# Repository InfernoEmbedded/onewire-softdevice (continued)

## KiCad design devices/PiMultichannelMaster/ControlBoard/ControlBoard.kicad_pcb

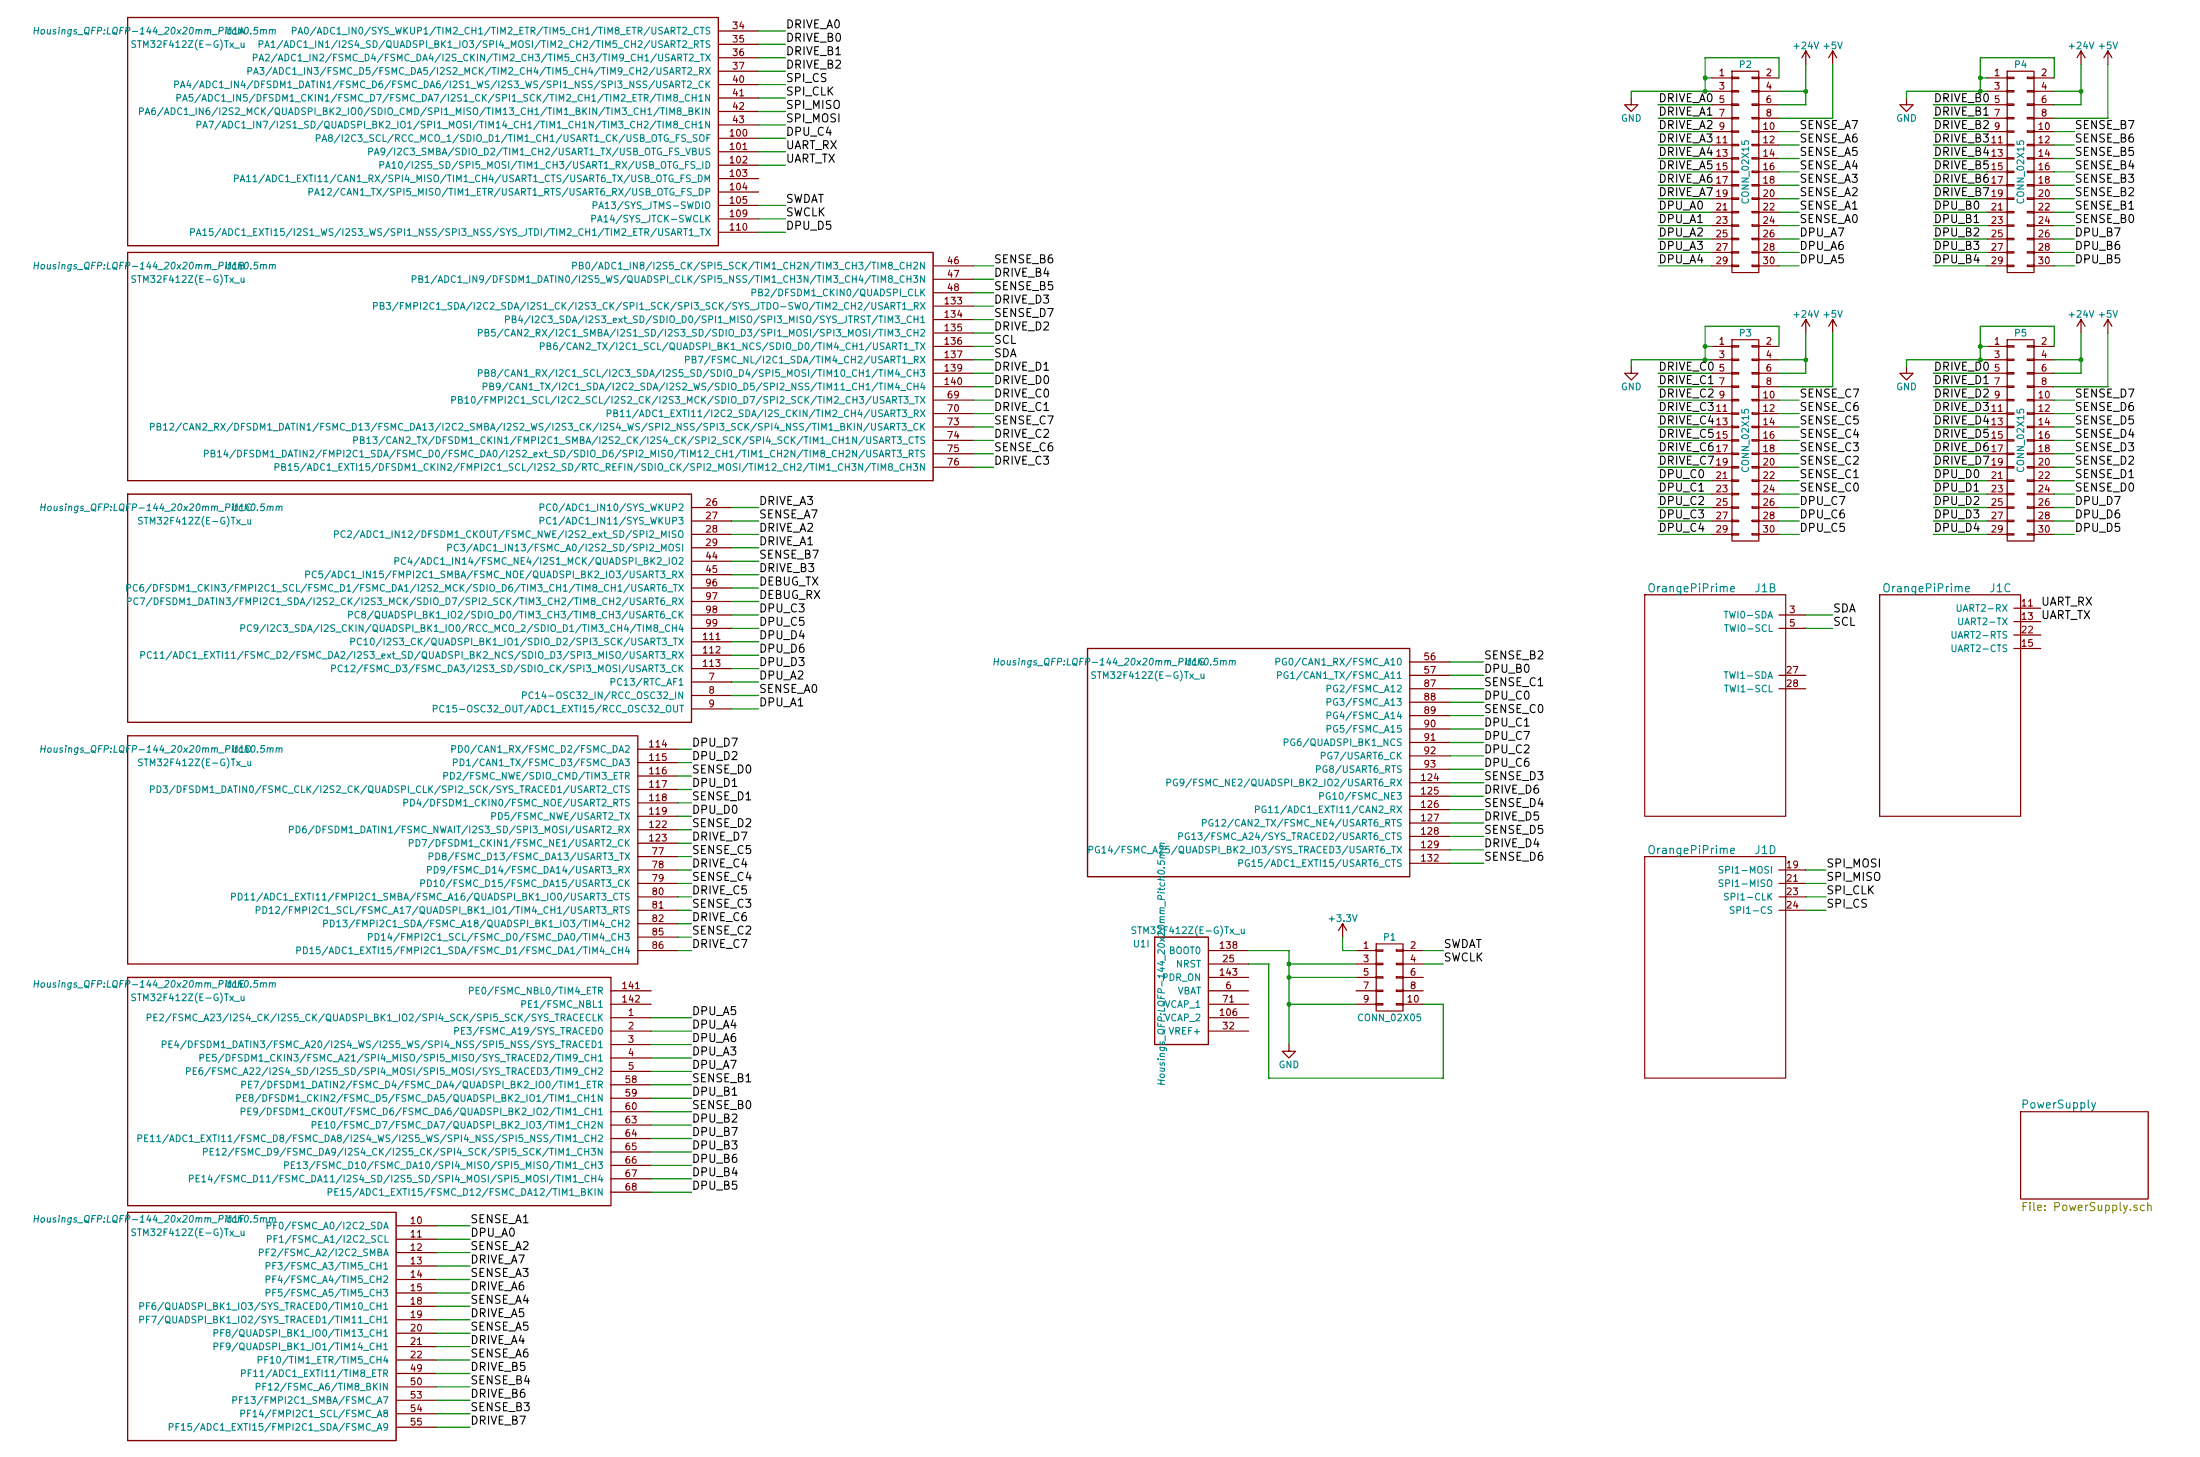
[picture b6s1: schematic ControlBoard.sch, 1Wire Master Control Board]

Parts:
J1: OrangePiPrime
P1: CONN_02X05; Pin_Header_Straight_2x05_Pitch2.54mm_SMD
P2, P3, P4, P5: CONN_02X15; Pin_Header_Straight_2x15_Pitch2.54mm_SMD
U1: STM32F412Z(E-G)Tx_u; LQFP-144_20x20mm_Pitch0.5mm

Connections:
+3V3: P1.1; also elsewhere on the board
+5V: P2.8, P3.8, P4.8, P5.8; also elsewhere on the board
+24V: P2.4, P2.6, P3.4, P3.6, P4.4, P4.6, P5.4, P5.6; also elsewhere on the board
/DPU_A0: P2.21, U1.11 (PF1/FSMC_A1/I2C2_SCL)
/DPU_A1: P2.23, U1.9 (PC15-OSC32_OUT/ADC1_EXTI15/RCC_OSC32_OUT)
/DPU_A2: P2.25, U1.7 (PC13/RTC_AF1)
/DPU_A3: P2.27, U1.4 (PE5/DFSDM1_CKIN3/FSMC_A21/SPI4_MISO/SPI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)
/DPU_A4: P2.29, U1.2 (PE3/FSMC_A19/SYS_TRACED0)
/DPU_A5: P2.30, U1.1 (PE2/FSMC_A23/I2S4_CK/I2S5_CK/QUADSPI_BK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)
/DPU_A6: P2.28, U1.3 (PE4/DFSDM1_DATIN3/FSMC_A20/I2S4_WS/I2S5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)
/DPU_A7: P2.26, U1.5 (PE6/FSMC_A22/I2S4_SD/I2S5_SD/SPI4_MOSI/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)
/DPU_B0: P4.21, U1.57 (PG1/CAN1_TX/FSMC_A11)
/DPU_B1: P4.23, U1.59 (PE8/DFSDM1_CKIN2/FSMC_D5/FSMC_DA5/QUADS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)
/DPU_B2: P4.25, U1.63 (PE10/FSMC_D7/FSMC_DA7/QUADSPI_BK2_IO3/T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)
/DPU_B3: P4.27, U1.65 (PE12/FSMC_D9/FSMC_DA9/I2S4_CK/I2S5_CK/S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)
/DPU_B4: P4.29, U1.67 (PE14/FSMC_D11/FSMC_DA11/I2S4_SD/I2S5_SD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)
/DPU_B5: P4.30, U1.68 (PE15/ADC1_EXTI15/FSMC_D12/FSMC_DA12/TIM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)
/DPU_B6: P4.28, U1.66 (PE13/FSMC_D10/FSMC_DA10/SPI4_MISO/SPI5_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)
/DPU_B7: P4.26, U1.64 (PE11/ADC1_EXTI11/FSMC_D8/FSMC_DA8/I2S4_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)
/DPU_C0: P3.21, U1.88 (PG3/FSMC_A13)
/DPU_C1: P3.23, U1.90 (PG5/FSMC_A15)
/DPU_C2: P3.25, U1.92 (PG7/USART6_CK)
/DPU_C3: P3.27, U1.98 (PC8/QUADSPI_BK1_IO2/SDIO_D0/TIM3_CH3/TI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)
/DPU_C4: P3.29, U1.100 (PA8/I2C3_SCL/RCC_MCO_1/SDIO_D1/TIM1_CH1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)
/DPU_C5: P3.30, U1.99 (PC9/I2C3_SDA/I2S_CKIN/QUADSPI_BK1_IO0/R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)
/DPU_C6: P3.28, U1.93 (PG8/USART6_RTS)
/DPU_C7: P3.26, U1.91 (PG6/QUADSPI_BK1_NCS)
/DPU_D0: P5.21, U1.119 (PD5/FSMC_NWE/USART2_TX)
/DPU_D1: P5.23, U1.117 (PD3/DFSDM1_DATIN0/FSMC_CLK/I2S2_CK/QUAD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)
/DPU_D2: P5.25, U1.115 (PD1/CAN1_TX/FSMC_D3/FSMC_DA3)
/DPU_D3: P5.27, U1.113 (PC12/FSMC_D3/FSMC_DA3/I2S3_SD/SDIO_CK/S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)
/DPU_D4: P5.29, U1.111 (PC10/I2S3_CK/QUADSPI_BK1_IO1/SDIO_D2/SP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)
/DPU_D5: P5.30, U1.110 (PA15/ADC1_EXTI15/I2S1_WS/I2S3_WS/SPI1_N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)
/DPU_D6: P5.28, U1.112 (PC11/ADC1_EXTI11/FSMC_D2/FSMC_DA2/I2S3_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)
/DPU_D7: P5.26, U1.114 (PD0/CAN1_RX/FSMC_D2/FSMC_DA2)
/DRIVE_A0: P2.5, U1.34 (PA0/ADC1_IN0/SYS_WKUP1/TIM2_CH1/TIM2_ET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)
/DRIVE_A1: P2.7, U1.29 (PC3/ADC1_IN13/FSMC_A0/I2S2_SD/SPI2_MOSI)
/DRIVE_A2: P2.9, U1.28 (PC2/ADC1_IN12/DFSDM1_CKOUT/FSMC_NWE/I2S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)
/DRIVE_A3: P2.11, U1.26 (PC0/ADC1_IN10/SYS_WKUP2)
/DRIVE_A4: P2.13, U1.21 (PF9/QUADSPI_BK1_IO1/TIM14_CH1)
/DRIVE_A5: P2.15, U1.19 (PF7/QUADSPI_BK1_IO2/SYS_TRACED1/TIM11_C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)
/DRIVE_A6: P2.17, U1.15 (PF5/FSMC_A5/TIM5_CH3)
/DRIVE_A7: P2.19, U1.13 (PF3/FSMC_A3/TIM5_CH1)
/DRIVE_B0: P4.5, U1.35 (PA1/ADC1_IN1/I2S4_SD/QUADSPI_BK1_IO3/SP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)
/DRIVE_B1: P4.7, U1.36 (PA2/ADC1_IN2/FSMC_D4/FSMC_DA4/I2S_CKIN/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)
/DRIVE_B2: P4.9, U1.37 (PA3/ADC1_IN3/FSMC_D5/FSMC_DA5/I2S2_MCK/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)
/DRIVE_B3: P4.11, U1.45 (PC5/ADC1_IN15/FMPI2C1_SMBA/FSMC_NOE/QUA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)
/DRIVE_B4: P4.13, U1.47 (PB1/ADC1_IN9/DFSDM1_DATIN0/I2S5_WS/QUAD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)
/DRIVE_B5: P4.15, U1.49 (PF11/ADC1_EXTI11/TIM8_ETR)
/DRIVE_B6: P4.17, U1.53 (PF13/FMPI2C1_SMBA/FSMC_A7)
/DRIVE_B7: P4.19, U1.55 (PF15/ADC1_EXTI15/FMPI2C1_SDA/FSMC_A9)
/DRIVE_C0: P3.5, U1.69 (PB10/FMPI2C1_SCL/I2C2_SCL/I2S2_CK/I2S3_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)
/DRIVE_C1: P3.7, U1.70 (PB11/ADC1_EXTI11/I2C2_SDA/I2S_CKIN/TIM2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)
/DRIVE_C2: P3.9, U1.74 (PB13/CAN2_TX/DFSDM1_CKIN1/FMPI2C1_SMBA/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)
/DRIVE_C3: P3.11, U1.76 (PB15/ADC1_EXTI15/DFSDM1_CKIN2/FMPI2C1_S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)
/DRIVE_C4: P3.13, U1.78 (PD9/FSMC_D14/FSMC_DA14/USART3_RX)
/DRIVE_C5: P3.15, U1.80 (PD11/ADC1_EXTI11/FMPI2C1_SMBA/FSMC_A16/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)
/DRIVE_C6: P3.17, U1.82 (PD13/FMPI2C1_SDA/FSMC_A18/QUADSPI_BK1_I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)
/DRIVE_C7: P3.19, U1.86 (PD15/ADC1_EXTI15/FMPI2C1_SDA/FSMC_D1/FS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)
/DRIVE_D0: P5.5, U1.140 (PB9/CAN1_TX/I2C1_SDA/I2C2_SDA/I2S2_WS/S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)
/DRIVE_D1: P5.7, U1.139 (PB8/CAN1_RX/I2C1_SCL/I2C3_SDA/I2S5_SD/S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)
/DRIVE_D2: P5.9, U1.135 (PB5/CAN2_RX/I2C1_SMBA/I2S1_SD/I2S3_SD/S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)
/DRIVE_D3: P5.11, U1.133 (PB3/FMPI2C1_SDA/I2C2_SDA/I2S1_CK/I2S3_C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)
/DRIVE_D4: P5.13, U1.129 (PG14/FSMC_A25/QUADSPI_BK2_IO3/SYS_TRACE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)
/DRIVE_D5: P5.15, U1.127 (PG12/CAN2_TX/FSMC_NE4/USART6_RTS)
/DRIVE_D6: P5.17, U1.125 (PG10/FSMC_NE3)
/DRIVE_D7: P5.19, U1.123 (PD7/DFSDM1_CKIN1/FSMC_NE1/USART2_CK)
/SCL: J1.5 (TWI0-SCL), U1.136 (PB6/CAN2_TX/I2C1_SCL/QUADSPI_BK1_NCS/SD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)
/SDA: J1.3 (TWI0-SDA), U1.137 (PB7/FSMC_NL/I2C1_SDA/TIM4_CH2/USART1_RX)
/SENSE_A0: P2.24, U1.8 (PC14-OSC32_IN/RCC_OSC32_IN)
/SENSE_A1: P2.22, U1.10 (PF0/FSMC_A0/I2C2_SDA)
/SENSE_A2: P2.20, U1.12 (PF2/FSMC_A2/I2C2_SMBA)
/SENSE_A3: P2.18, U1.14 (PF4/FSMC_A4/TIM5_CH2)
/SENSE_A4: P2.16, U1.18 (PF6/QUADSPI_BK1_IO3/SYS_TRACED0/TIM10_C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)
/SENSE_A5: P2.14, U1.20 (PF8/QUADSPI_BK1_IO0/TIM13_CH1)
/SENSE_A6: P2.12, U1.22 (PF10/TIM1_ETR/TIM5_CH4)
/SENSE_A7: P2.10, U1.27 (PC1/ADC1_IN11/SYS_WKUP3)
/SENSE_B0: P4.24, U1.60 (PE9/DFSDM1_CKOUT/FSMC_D6/FSMC_DA6/QUADS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)
/SENSE_B1: P4.22, U1.58 (PE7/DFSDM1_DATIN2/FSMC_D4/FSMC_DA4/QUAD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)
/SENSE_B2: P4.20, U1.56 (PG0/CAN1_RX/FSMC_A10)
/SENSE_B3: P4.18, U1.54 (PF14/FMPI2C1_SCL/FSMC_A8)
/SENSE_B4: P4.16, U1.50 (PF12/FSMC_A6/TIM8_BKIN)
/SENSE_B5: P4.14, U1.48 (PB2/DFSDM1_CKIN0/QUADSPI_CLK)
/SENSE_B6: P4.12, U1.46 (PB0/ADC1_IN8/I2S5_CK/SPI5_SCK/TIM1_CH2N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)
/SENSE_B7: P4.10, U1.44 (PC4/ADC1_IN14/FSMC_NE4/I2S1_MCK/QUADSPI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)
/SENSE_C0: P3.24, U1.89 (PG4/FSMC_A14)
/SENSE_C1: P3.22, U1.87 (PG2/FSMC_A12)
/SENSE_C2: P3.20, U1.85 (PD14/FMPI2C1_SCL/FSMC_D0/FSMC_DA0/TIM4_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)
/SENSE_C3: P3.18, U1.81 (PD12/FMPI2C1_SCL/FSMC_A17/QUADSPI_BK1_I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)
/SENSE_C4: P3.16, U1.79 (PD10/FSMC_D15/FSMC_DA15/USART3_CK)
/SENSE_C5: P3.14, U1.77 (PD8/FSMC_D13/FSMC_DA13/USART3_TX)
/SENSE_C6: P3.12, U1.75 (PB14/DFSDM1_DATIN2/FMPI2C1_SDA/FSMC_D0/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)
/SENSE_C7: P3.10, U1.73 (PB12/CAN2_RX/DFSDM1_DATIN1/FSMC_D13/FSM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)
/SENSE_D0: P5.24, U1.116 (PD2/FSMC_NWE/SDIO_CMD/TIM3_ETR)
/SENSE_D1: P5.22, U1.118 (PD4/DFSDM1_CKIN0/FSMC_NOE/USART2_RTS)
/SENSE_D2: P5.20, U1.122 (PD6/DFSDM1_DATIN1/FSMC_NWAIT/I2S3_SD/SP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)
/SENSE_D3: P5.18, U1.124 (PG9/FSMC_NE2/QUADSPI_BK2_IO2/USART6_RX)
/SENSE_D4: P5.16, U1.126 (PG11/ADC1_EXTI11/CAN2_RX)
/SENSE_D5: P5.14, U1.128 (PG13/FSMC_A24/SYS_TRACED2/USART6_CTS)
/SENSE_D6: P5.12, U1.132 (PG15/ADC1_EXTI15/USART6_CTS)
/SENSE_D7: P5.10, U1.134 (PB4/I2C3_SDA/I2S3_ext_SD/SDIO_D0/SPI1_M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)
/SPI_CLK: J1.23 (SPI1-CLK), U1.41 (PA5/ADC1_IN5/DFSDM1_CKIN1/FSMC_D7/FSMC_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)
/SPI_CS: J1.24 (SPI1-CS), U1.40 (PA4/ADC1_IN4/DFSDM1_DATIN1/FSMC_D6/FSMC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)
/SPI_MISO: J1.21 (SPI1-MISO), U1.42 (PA6/ADC1_IN6/I2S2_MCK/QUADSPI_BK2_IO0/S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)
/SPI_MOSI: J1.19 (SPI1-MOSI), U1.43 (PA7/ADC1_IN7/I2S1_SD/QUADSPI_BK2_IO1/SP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)
/SWCLK: P1.4, U1.109 (PA14/SYS_JTCK-SWCLK)
/SWDAT: P1.2, U1.105 (PA13/SYS_JTMS-SWDIO)
/UART_RX: J1.11 (UART2-RX), U1.101 (PA9/I2C3_SMBA/SDIO_D2/TIM1_CH2/USART1_T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)
/UART_TX: J1.13 (UART2-TX), U1.102 (PA10/I2S5_SD/SPI5_MOSI/TIM1_CH3/USART1_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)
GND: P1.3, P1.5, P1.9, P2.1, P2.2, P2.3, P3.1, P3.2, P3.3, P4.1, P4.2, P4.3, P5.1, P5.2, P5.3, U1.138 (BOOT0); also elsewhere on the board
unnamed: P1.10, U1.25 (NRST)

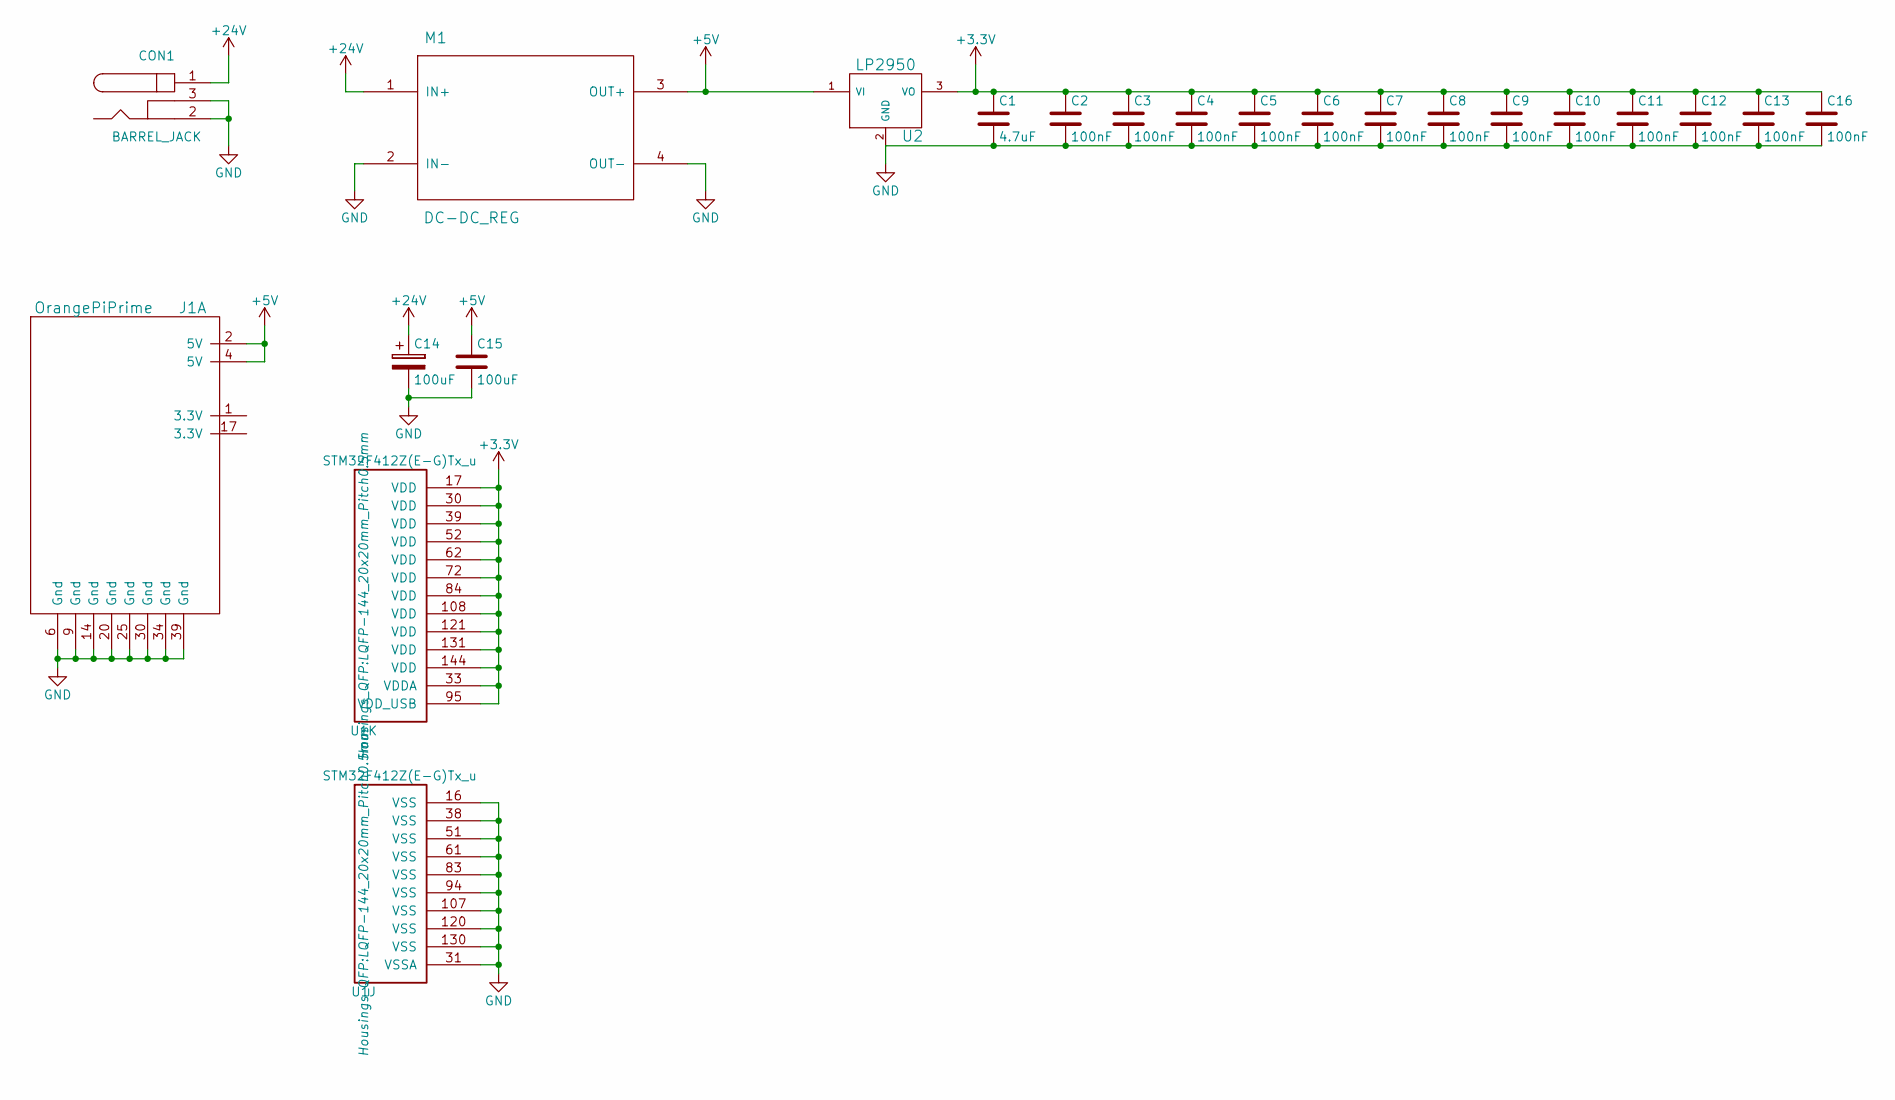
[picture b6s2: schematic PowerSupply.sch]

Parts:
C1: 4.7uF; C_0603
C2, C3, C4, C5, C6, C7, C8, C9, C10, C11, C12, C13, C16: 100nF; C_0603
C14: 100uF; CP_Elec_8x10
C15: 100uF; C_1206
CON1: BARREL_JACK
J1: OrangePiPrime
M1: DC-DC_REG; D-SUN_DC_DC
U1: STM32F412Z(E-G)Tx_u; LQFP-144_20x20mm_Pitch0.5mm
U2: LP2950; TO-252-2

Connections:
+3V3: C1.1, C2.1, C3.1, C4.1, C5.1, C6.1, C7.1, C8.1, C9.1, C10.1, C11.1, C12.1, C13.1, C16.1, U1.17 (VDD), U1.30 (VDD), U1.33 (VDDA), U1.39 (VDD), U1.52 (VDD), U1.62 (VDD), U1.72 (VDD), U1.84 (VDD), U1.95 (VDD_USB), U1.108 (VDD), U1.121 (VDD), U1.131 (VDD), U1.144 (VDD), U2.3 (VO); also elsewhere on the board
+5V: C15.1, J1.2 (5V), J1.4 (5V), M1.3 (OUT+), U2.1 (VI); also elsewhere on the board
+24V: C14.1, CON1.1, M1.1 (IN+); also elsewhere on the board
GND: C1.2, C2.2, C3.2, C4.2, C5.2, C6.2, C7.2, C8.2, C9.2, C10.2, C11.2, C12.2, C13.2, C14.2, C15.2, C16.2, CON1.2, CON1.3, J1.6 (Gnd), J1.9 (Gnd), J1.14 (Gnd), J1.20 (Gnd), J1.25 (Gnd), J1.30 (Gnd), J1.34 (Gnd), J1.39 (Gnd), M1.2 (IN-), M1.4 (OUT-), U1.16 (VSS), U1.31 (VSSA), U1.38 (VSS), U1.51 (VSS), U1.61 (VSS), U1.83 (VSS), U1.94 (VSS), U1.107 (VSS), U1.120 (VSS), U1.130 (VSS), U2.2 (GND); also elsewhere on the board

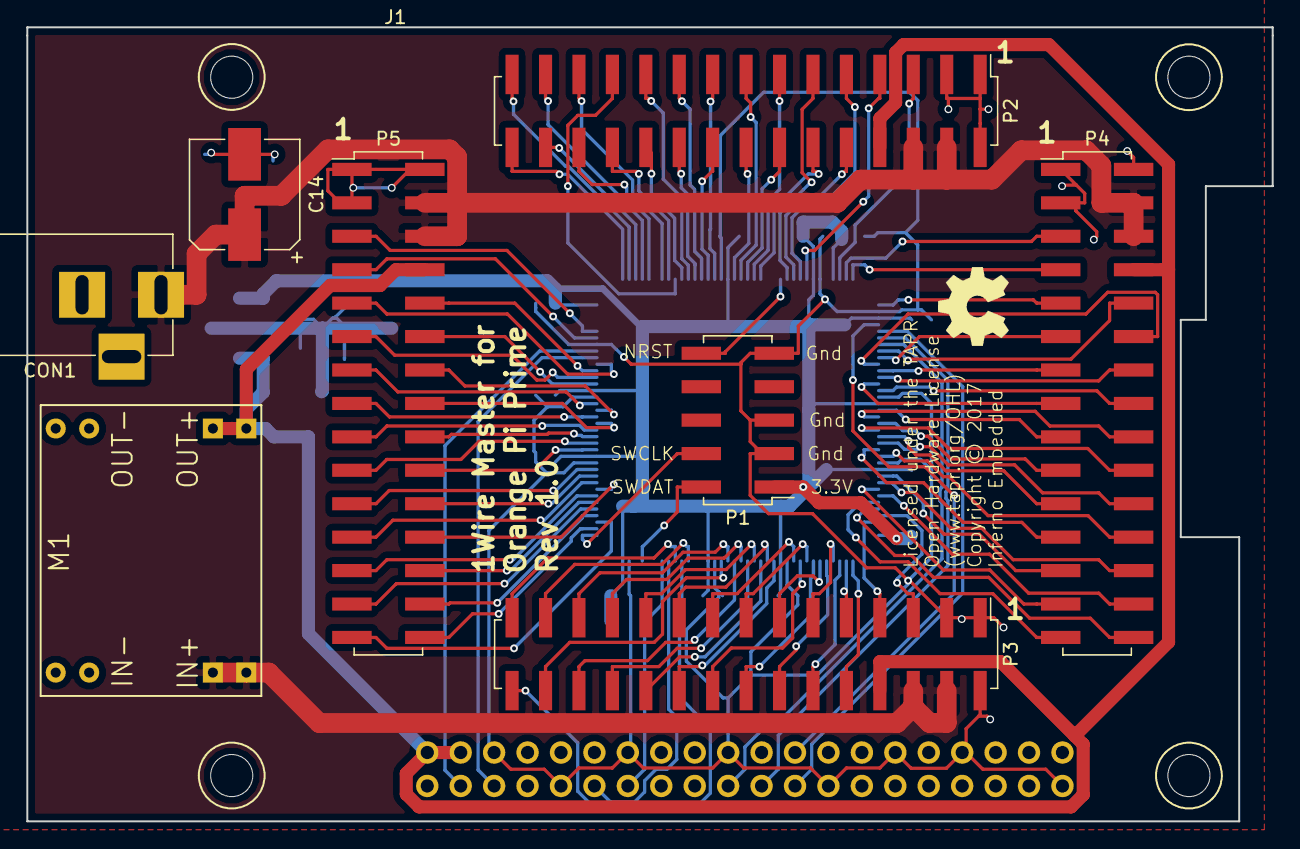
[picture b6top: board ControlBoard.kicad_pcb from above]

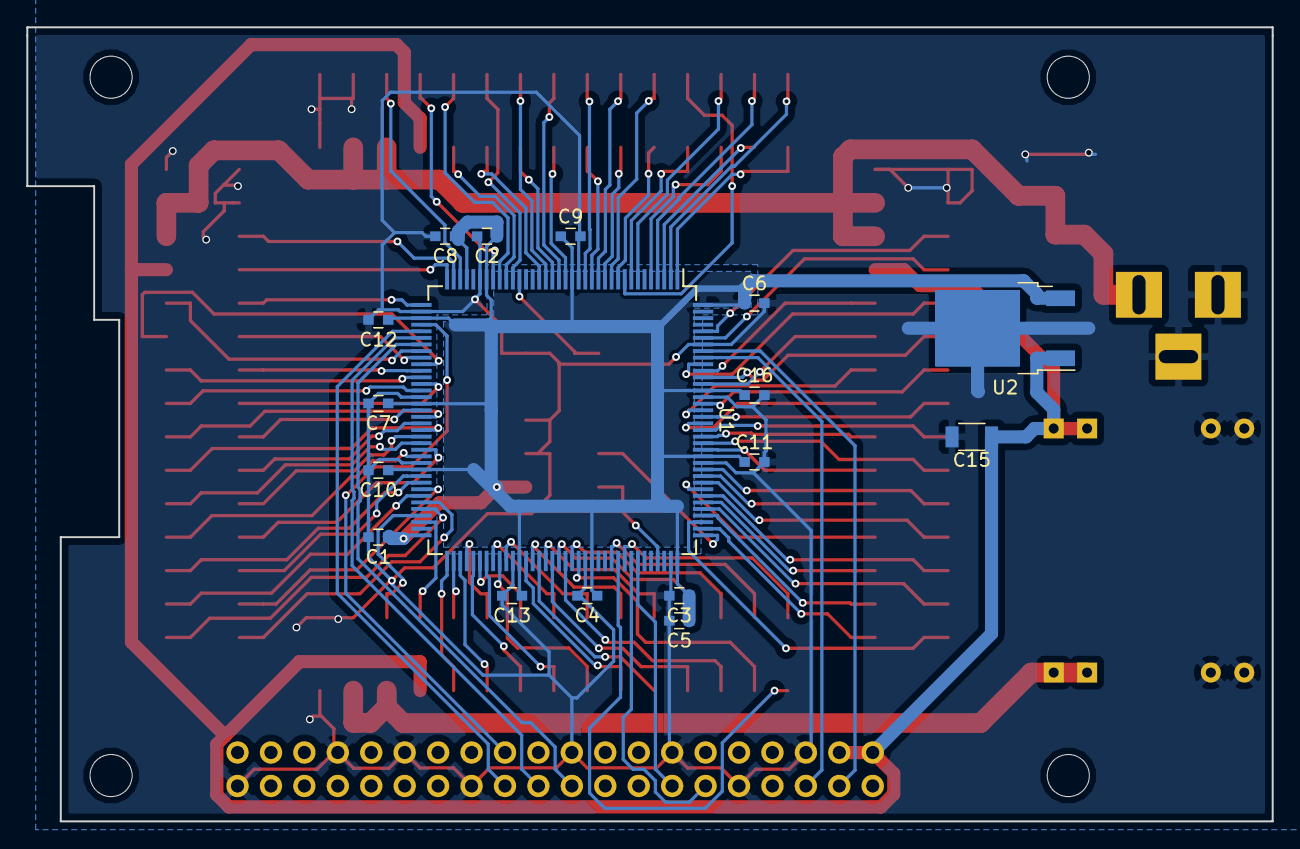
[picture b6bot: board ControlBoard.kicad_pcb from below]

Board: 2 copper layers, 94.6 x 60.3 mm, 30 parts (17 on the bottom side), 111 nets.

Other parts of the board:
REF1, REF2, REF3, REF4: MountingHole_3.2mm_M3

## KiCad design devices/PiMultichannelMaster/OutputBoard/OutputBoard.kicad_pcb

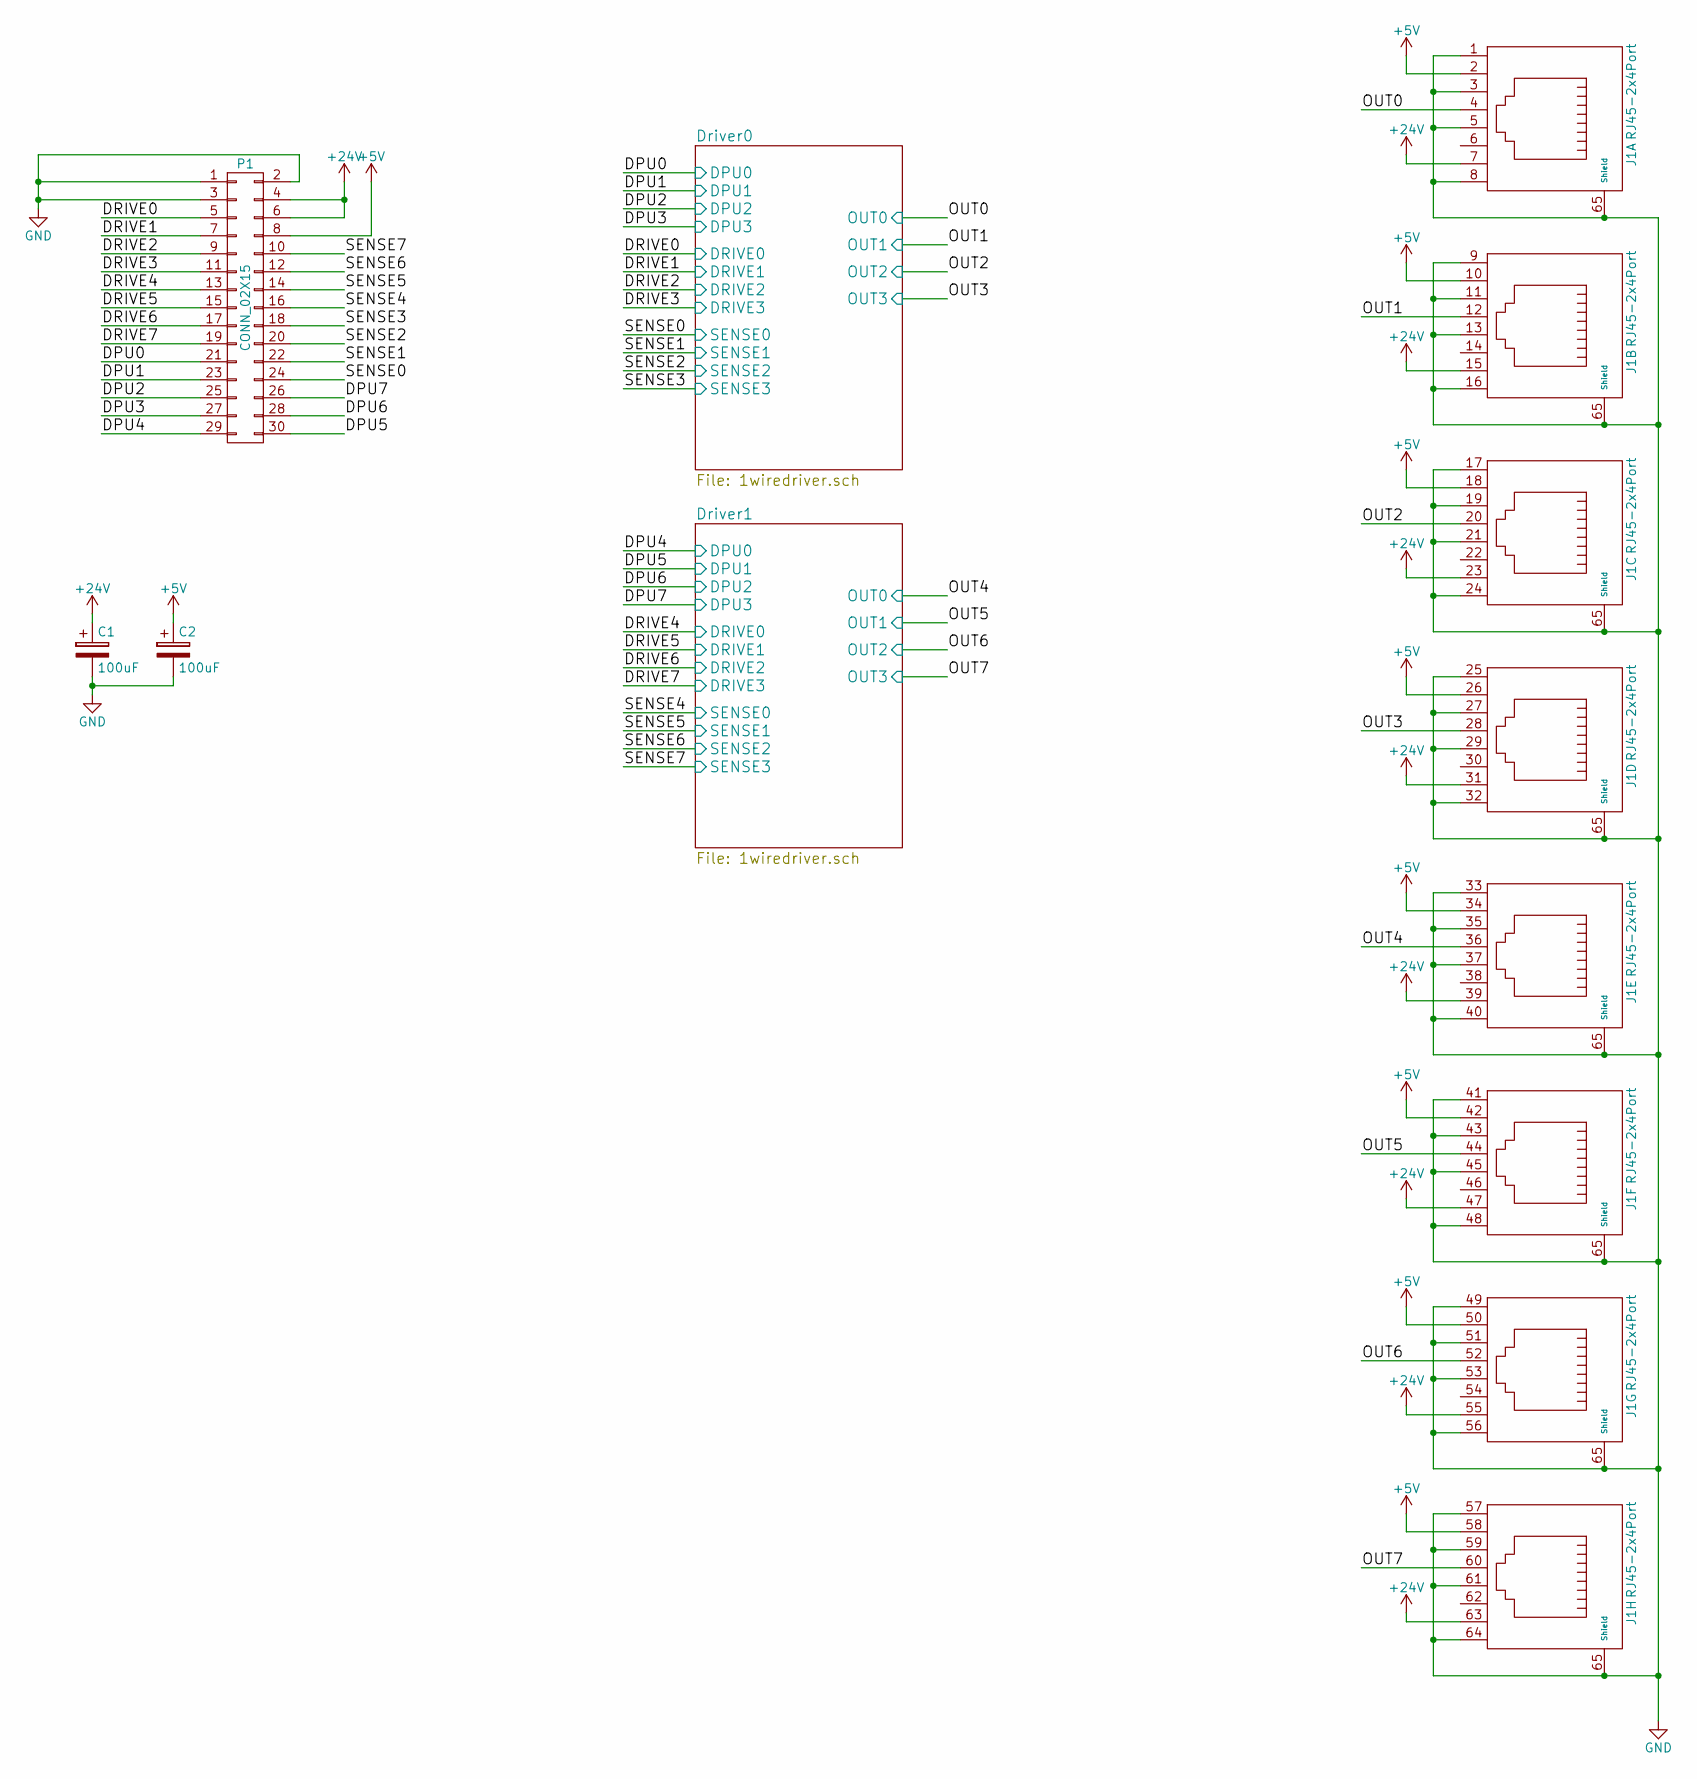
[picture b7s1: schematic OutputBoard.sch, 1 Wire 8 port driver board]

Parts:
C1, C2: 100uF; C_1206
J1: RJ45-2x4Port; RJ45-2x4-R
P1: CONN_02X15; Pin_Header_Straight_2x15_Pitch2.54mm

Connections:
+5V: C2.1, J1.2, J1.10, J1.18, J1.26, J1.34, J1.42, J1.50, J1.58, P1.8; also elsewhere on the board
+24V: C1.1, J1.7, J1.15, J1.23, J1.31, J1.39, J1.47, J1.55, J1.63, P1.4, P1.6
/DPU0: P1.21; also elsewhere on the board
/DPU1: P1.23; also elsewhere on the board
/DPU2: P1.25; also elsewhere on the board
/DPU3: P1.27; also elsewhere on the board
/DPU4: P1.29; also elsewhere on the board
/DPU5: P1.30; also elsewhere on the board
/DPU6: P1.28; also elsewhere on the board
/DPU7: P1.26; also elsewhere on the board
/DRIVE0: P1.5; also elsewhere on the board
/DRIVE1: P1.7; also elsewhere on the board
/DRIVE2: P1.9; also elsewhere on the board
/DRIVE3: P1.11; also elsewhere on the board
/DRIVE4: P1.13; also elsewhere on the board
/DRIVE5: P1.15; also elsewhere on the board
/DRIVE6: P1.17; also elsewhere on the board
/DRIVE7: P1.19; also elsewhere on the board
/OUT0: J1.4; also elsewhere on the board
/OUT1: J1.12; also elsewhere on the board
/OUT2: J1.20; also elsewhere on the board
/OUT3: J1.28; also elsewhere on the board
/OUT4: J1.36; also elsewhere on the board
/OUT5: J1.44; also elsewhere on the board
/OUT6: J1.52; also elsewhere on the board
/OUT7: J1.60; also elsewhere on the board
/SENSE0: P1.24; also elsewhere on the board
/SENSE1: P1.22; also elsewhere on the board
/SENSE2: P1.20; also elsewhere on the board
/SENSE3: P1.18; also elsewhere on the board
/SENSE4: P1.16; also elsewhere on the board
/SENSE5: P1.14; also elsewhere on the board
/SENSE6: P1.12; also elsewhere on the board
/SENSE7: P1.10; also elsewhere on the board
GND: C1.2, C2.2, J1.1, J1.3, J1.5, J1.8, J1.9, J1.11, J1.13, J1.16, J1.17, J1.19, J1.21, J1.24, J1.25, J1.27, J1.29, J1.32, J1.33, J1.35, J1.37, J1.40, J1.41, J1.43, J1.45, J1.48, J1.49, J1.51, J1.53, J1.56, J1.57, J1.59, J1.61, J1.64, J1.65 (Shield), P1.1, P1.2, P1.3; also elsewhere on the board

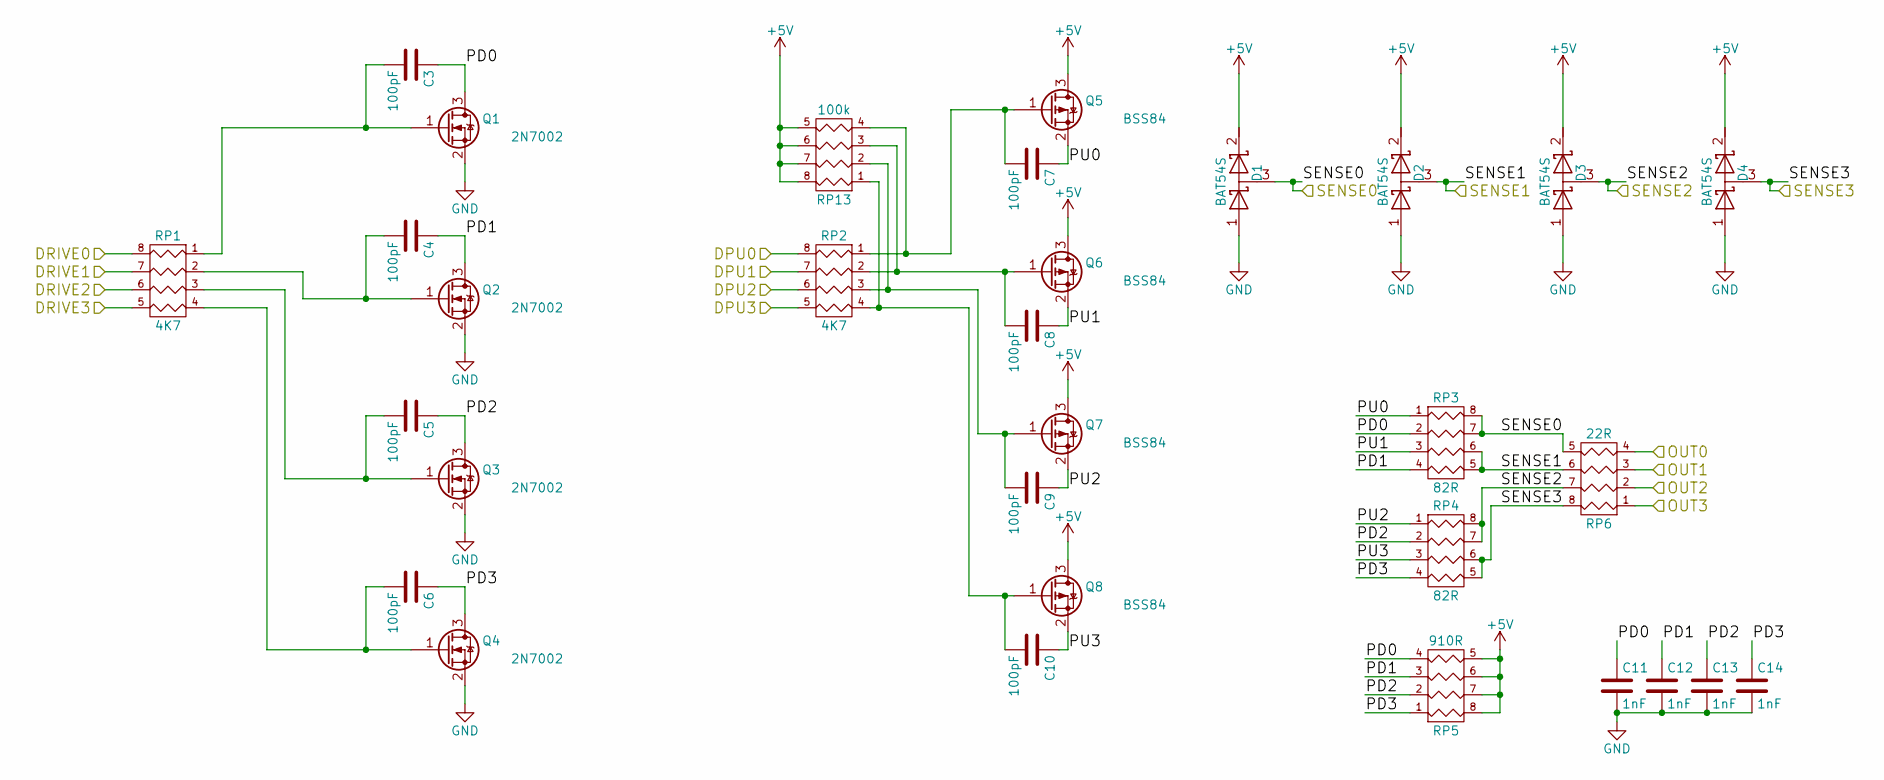
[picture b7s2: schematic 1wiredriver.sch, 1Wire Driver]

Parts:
C3, C4, C5, C6, C7, C8, C9, C10: 100pF; C_0603
C11, C12, C13, C14: 1nF; C_0603
D1, D2, D3, D4: BAT54S; SOT-23
Q1, Q2, Q3, Q4: 2N7002; SOT-23
Q5, Q6, Q7, Q8: BSS84; SOT-23
RP1, RP2: 4K7; 0603_Pack4
RP3, RP4: 82R; 0603_Pack4
RP5: 910R; 0603_Pack4
RP6: 22R; 0603_Pack4
RP13: 100k; 0603_Pack4

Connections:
+5V: D1.2 (K), D2.2 (K), D3.2 (K), D4.2 (K), Q5.3 (D), Q6.3 (D), Q7.3 (D), Q8.3 (D), RP5.5 (R4), RP5.6 (R3), RP5.7 (R2), RP5.8 (R1), RP13.5 (R4), RP13.6 (R3), RP13.7 (R2), RP13.8 (R1); also elsewhere on the board
/DPU0: RP2.8 (R1); also elsewhere on the board
/DPU1: RP2.7 (R2); also elsewhere on the board
/DPU2: RP2.6 (R3); also elsewhere on the board
/DPU3: RP2.5 (R4); also elsewhere on the board
/DRIVE0: RP1.8 (R1); also elsewhere on the board
/DRIVE1: RP1.7 (R2); also elsewhere on the board
/DRIVE2: RP1.6 (R3); also elsewhere on the board
/DRIVE3: RP1.5 (R4); also elsewhere on the board
/Driver0/PD0: C3.1, C11.1, Q1.3 (D), RP3.2, RP5.4
/Driver0/PD1: C4.1, C12.1, Q2.3 (D), RP3.4, RP5.3
/Driver0/PD2: C5.1, C13.1, Q3.3 (D), RP4.2, RP5.2
/Driver0/PD3: C6.1, C14.1, Q4.3 (D), RP4.4, RP5.1
/Driver0/PU0: C7.1, Q5.2 (S), RP3.1
/Driver0/PU1: C8.1, Q6.2 (S), RP3.3
/Driver0/PU2: C9.1, Q7.2 (S), RP4.1
/Driver0/PU3: C10.1, Q8.2 (S), RP4.3
/OUT0: RP6.4; also elsewhere on the board
/OUT1: RP6.3; also elsewhere on the board
/OUT2: RP6.2; also elsewhere on the board
/OUT3: RP6.1; also elsewhere on the board
/SENSE0: D1.3 (common), RP3.7 (R2), RP3.8 (R1), RP6.5 (R4); also elsewhere on the board
/SENSE1: D2.3 (common), RP3.5 (R4), RP3.6 (R3), RP6.6 (R3); also elsewhere on the board
/SENSE2: D3.3 (common), RP4.7 (R2), RP4.8 (R1), RP6.7 (R2); also elsewhere on the board
/SENSE3: D4.3 (common), RP4.5 (R4), RP4.6 (R3), RP6.8 (R1); also elsewhere on the board
GND: C11.2, C12.2, C13.2, C14.2, D1.1 (A), D2.1 (A), D3.1 (A), D4.1 (A), Q1.2 (S), Q2.2 (S), Q3.2 (S), Q4.2 (S); also elsewhere on the board
unnamed: C3.2, Q1.1 (G), RP1.1
unnamed: C4.2, Q2.1 (G), RP1.2
unnamed: C5.2, Q3.1 (G), RP1.3
unnamed: C6.2, Q4.1 (G), RP1.4
unnamed: C7.2, Q5.1 (G), RP2.1, RP13.4
unnamed: C8.2, Q6.1 (G), RP2.2, RP13.3
unnamed: C9.2, Q7.1 (G), RP2.3, RP13.2
unnamed: C10.2, Q8.1 (G), RP2.4, RP13.1

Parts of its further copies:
C15, C16, C17, C18, C19, C20, C21, C22: 100pF; C_0603
C23, C24, C25, C26: 1nF; C_0603
D5, D6, D7, D8: BAT54S; SOT-23
Q9, Q10, Q11, Q12: 2N7002; SOT-23
Q13, Q14, Q15, Q16: BSS84; SOT-23
RP7, RP8: 4K7; 0603_Pack4
RP9, RP10: 82R; 0603_Pack4
RP11: 910R; 0603_Pack4
RP12: 22R; 0603_Pack4
RP14: 100k; 0603_Pack4

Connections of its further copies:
+5V: D5.2 (K), D6.2 (K), D7.2 (K), D8.2 (K), Q13.3 (D), Q14.3 (D), Q15.3 (D), Q16.3 (D), RP11.5 (R4), RP11.6 (R3), RP11.7 (R2), RP11.8 (R1), RP14.5 (R4), RP14.6 (R3), RP14.7 (R2), RP14.8 (R1); also elsewhere on the board
/DPU4: RP8.8 (R1); also elsewhere on the board
/DPU5: RP8.7 (R2); also elsewhere on the board
/DPU6: RP8.6 (R3); also elsewhere on the board
/DPU7: RP8.5 (R4); also elsewhere on the board
/DRIVE4: RP7.8 (R1); also elsewhere on the board
/DRIVE5: RP7.7 (R2); also elsewhere on the board
/DRIVE6: RP7.6 (R3); also elsewhere on the board
/DRIVE7: RP7.5 (R4); also elsewhere on the board
/Driver1/PD0: C15.1, C23.1, Q9.3 (D), RP9.2, RP11.4
/Driver1/PD1: C16.1, C24.1, Q10.3 (D), RP9.4, RP11.3
/Driver1/PD2: C17.1, C25.1, Q11.3 (D), RP10.2, RP11.2
/Driver1/PD3: C18.1, C26.1, Q12.3 (D), RP10.4, RP11.1
/Driver1/PU0: C19.1, Q13.2 (S), RP9.1
/Driver1/PU1: C20.1, Q14.2 (S), RP9.3
/Driver1/PU2: C21.1, Q15.2 (S), RP10.1
/Driver1/PU3: C22.1, Q16.2 (S), RP10.3
/OUT4: RP12.4; also elsewhere on the board
/OUT5: RP12.3; also elsewhere on the board
/OUT6: RP12.2; also elsewhere on the board
/OUT7: RP12.1; also elsewhere on the board
/SENSE4: D5.3 (common), RP9.7 (R2), RP9.8 (R1), RP12.5 (R4); also elsewhere on the board
/SENSE5: D6.3 (common), RP9.5 (R4), RP9.6 (R3), RP12.6 (R3); also elsewhere on the board
/SENSE6: D7.3 (common), RP10.7 (R2), RP10.8 (R1), RP12.7 (R2); also elsewhere on the board
/SENSE7: D8.3 (common), RP10.5 (R4), RP10.6 (R3), RP12.8 (R1); also elsewhere on the board
GND: C23.2, C24.2, C25.2, C26.2, D5.1 (A), D6.1 (A), D7.1 (A), D8.1 (A), Q9.2 (S), Q10.2 (S), Q11.2 (S), Q12.2 (S); also elsewhere on the board
unnamed: C15.2, Q9.1 (G), RP7.1
unnamed: C16.2, Q10.1 (G), RP7.2
unnamed: C17.2, Q11.1 (G), RP7.3
unnamed: C18.2, Q12.1 (G), RP7.4
unnamed: C19.2, Q13.1 (G), RP8.1, RP14.4
unnamed: C20.2, Q14.1 (G), RP8.2, RP14.3
unnamed: C21.2, Q15.1 (G), RP8.3, RP14.2
unnamed: C22.2, Q16.1 (G), RP8.4, RP14.1
